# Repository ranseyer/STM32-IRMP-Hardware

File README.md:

View this project on [CADLAB.io](https://cadlab.io/project/2465). 

# STM32-IRMP-Hardware

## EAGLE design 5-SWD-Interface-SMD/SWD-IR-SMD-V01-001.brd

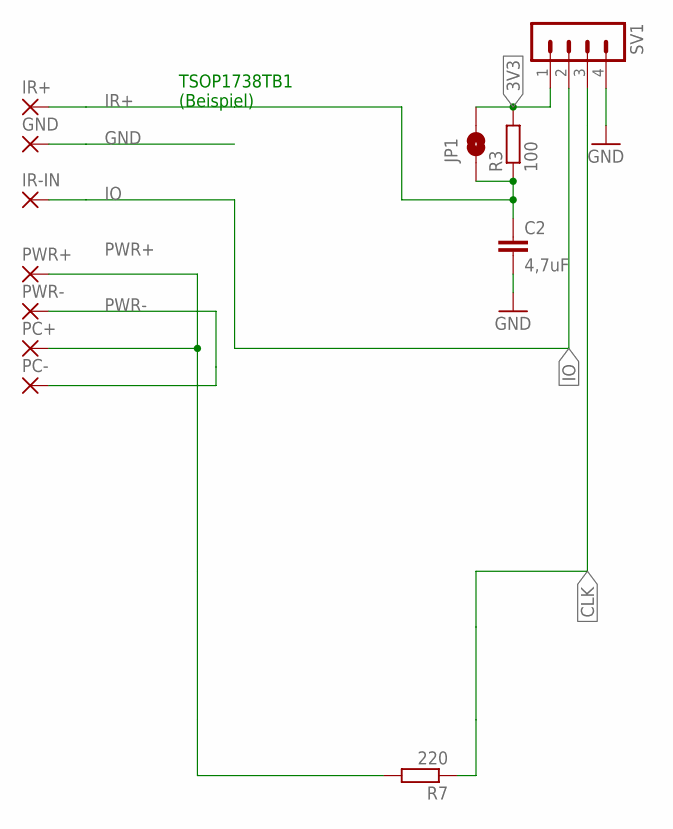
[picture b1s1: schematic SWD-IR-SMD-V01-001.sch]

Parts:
C2: 4,7uF; C1206K
GND: SMD2; SMD1,27-2,54
IR+: SMD2; SMD1,27-2,54
IR-IN: SMD2; SMD1,27-2,54
JP1: JUMPER-SMT_2_NO_NO-SILK; SMT-JUMPER_2_NO_NO-SILK
PC+: SMD2; SMD1,27-2,54
PC-: SMD2; SMD1,27-2,54
PWR+: SMD2; SMD1,27-2,54
PWR-: SMD2; SMD1,27-2,54
R3: 100; R0805W
R7: 220; R0805W
SV1: MA04-1

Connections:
3V3: JP1.2, R3.2, SV1.1
CLK: R7.1, SV1.3
GND: C2.2, GND.1, SV1.4
IO: IR-IN.1, SV1.2
IR+: C2.1, IR+.1, JP1.1, R3.1
PWR+: PC+.1, PWR+.1, R7.2
PWR-: PC-.1, PWR-.1

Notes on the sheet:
TSOP1738TB1 (Beispiel)

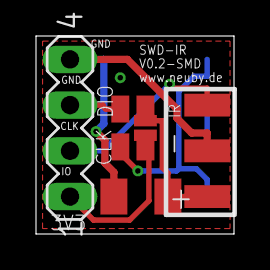
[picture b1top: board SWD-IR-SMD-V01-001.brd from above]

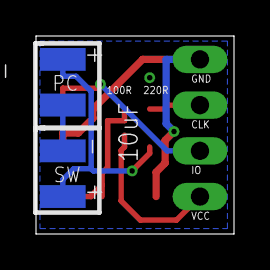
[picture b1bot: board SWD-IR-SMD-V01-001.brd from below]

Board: 2 copper layers, 11.0 x 11.0 mm, 12 parts (4 on the bottom side), 7 nets.

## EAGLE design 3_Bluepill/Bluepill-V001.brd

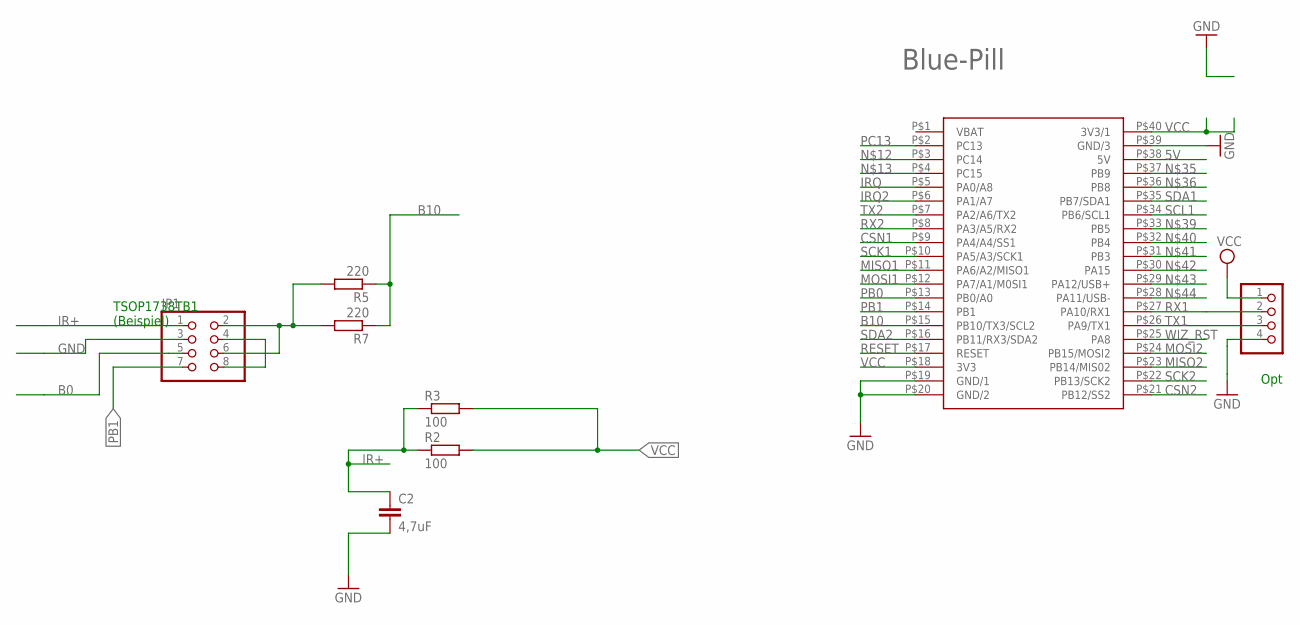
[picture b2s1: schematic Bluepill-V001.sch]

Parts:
C2: 4,7uF; C1206K
DBG: PINHD-1X04_2.54-S; 1X04-S
JP1: PINHD-2X4/90; 2X04/90
R2: 100; 0204/7
R3: 100; R0805W
R5: 220; 0204/7
R7: 220; R0805W
U$4: BLUEPILL

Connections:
5V: U$4.P$38 (5V)
B0: JP1.5
B10: R5.1, R7.1, U$4.P$15 (PB10/TX3/SCL2)
CSN1: U$4.P$9 (PA4/A4/SS1)
CSN2: U$4.P$21 (PB12/SS2)
GND: C2.2, DBG.4, JP1.3, U$4.P$19 (GND/1), U$4.P$20 (GND/2), U$4.P$39 (GND/3)
IR+: C2.1, JP1.1, R2.1, R3.1
IRQ: U$4.P$5 (PA0/A8)
IRQ2: U$4.P$6 (PA1/A7)
MISO1: U$4.P$11 (PA6/A2/MISO1)
MISO2: U$4.P$23 (PB14/MIS02)
MOSI1: U$4.P$12 (PA7/A1/M0SI1)
MOSI2: U$4.P$24 (PB15/MOSI2)
unnamed: JP1.4, JP1.8
unnamed: JP1.2, JP1.6, R5.2, R7.2
PB0: U$4.P$13 (PB0/A0)
PB1: JP1.7, U$4.P$14 (PB1)
PC13: U$4.P$2 (PC13)
RESET: U$4.P$17 (RESET)
RX1: DBG.2, U$4.P$27 (PA10/RX1)
RX2: U$4.P$8 (PA3/A5/RX2)
SCK1: U$4.P$10 (PA5/A3/SCK1)
SCK2: U$4.P$22 (PB13/SCK2)
SCL1: U$4.P$34 (PB6/SCL1)
SDA1: U$4.P$35 (PB7/SDA1)
SDA2: U$4.P$16 (PB11/RX3/SDA2)
TX1: DBG.3, U$4.P$26 (PA9/TX1)
TX2: U$4.P$7 (PA2/A6/TX2)
VCC: DBG.1, R2.2, R3.2, U$4.P$18 (3V3), U$4.P$40 (3V3/1)
WIZ_RST: U$4.P$25 (PA8)

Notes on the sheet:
TSOP1738TB1 (Beispiel)
Opt
Blue-Pill

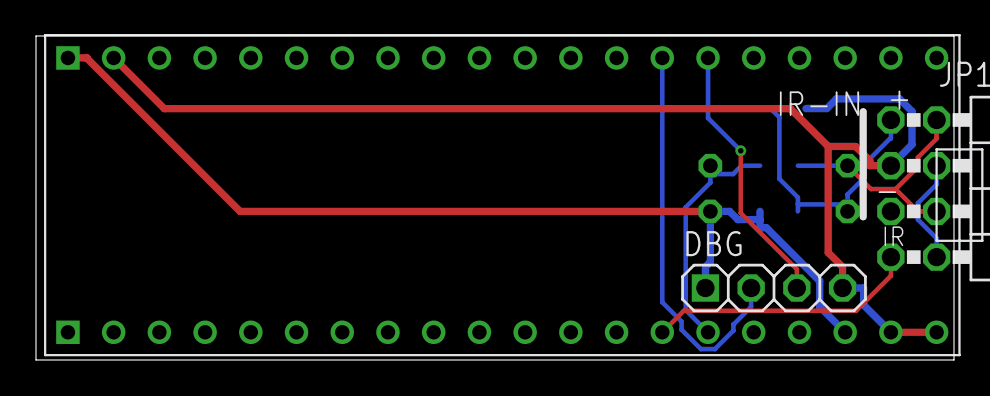
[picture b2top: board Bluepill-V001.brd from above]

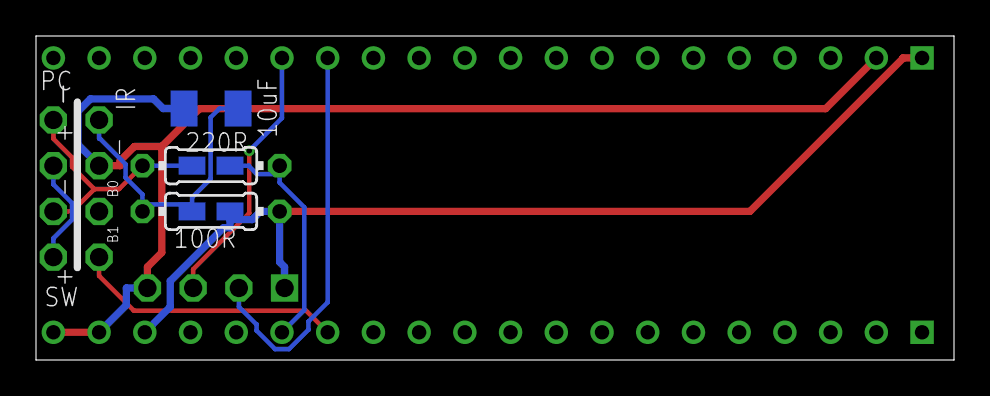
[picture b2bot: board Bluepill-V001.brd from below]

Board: 2 copper layers, 51.0 x 18.0 mm, 8 parts (5 on the bottom side), 9 nets.

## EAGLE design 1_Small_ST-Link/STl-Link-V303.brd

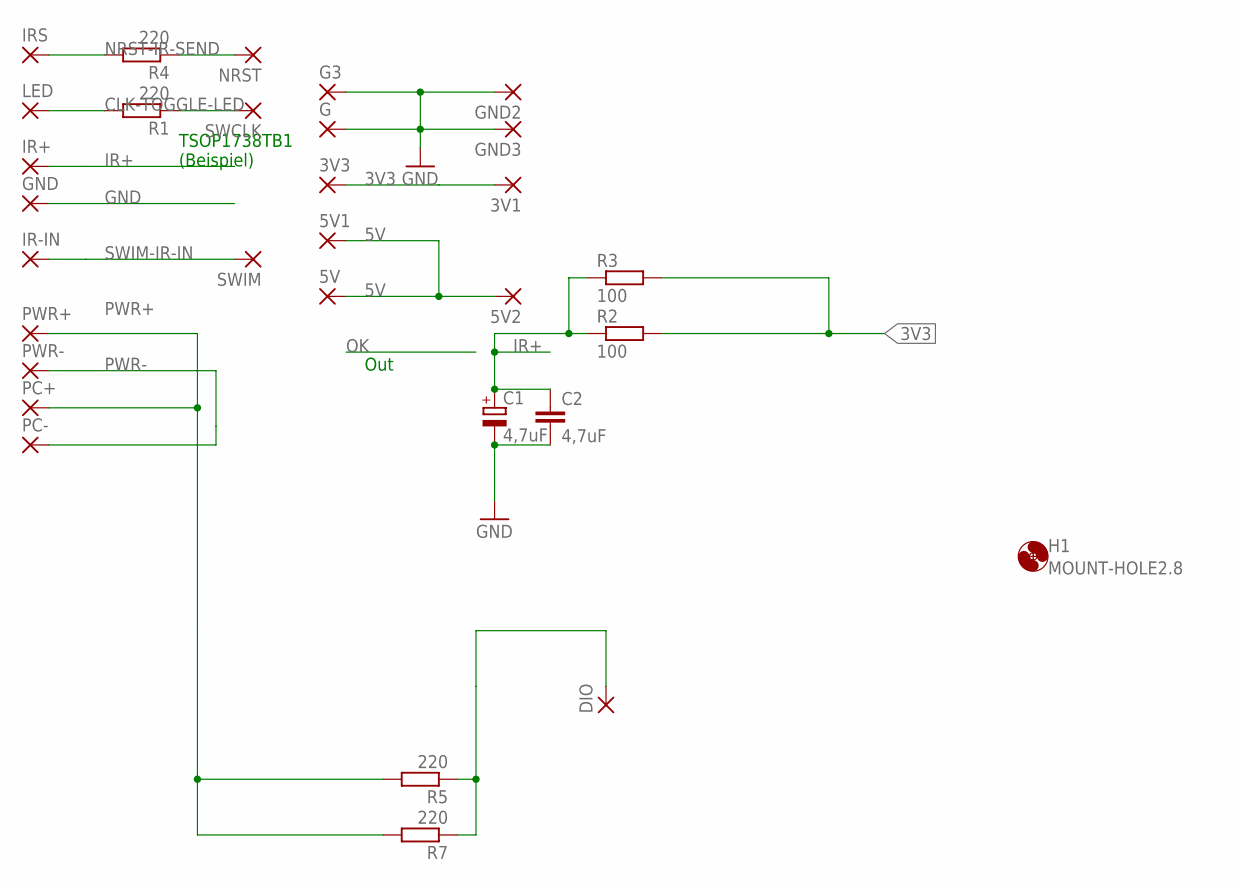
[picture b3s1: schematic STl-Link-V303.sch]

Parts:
3V1, 3V3, 5V, 5V1, 5V2: SMD2; SMD1,27-2,54
C1: 4,7uF; E1,8-4
C2: 4,7uF; C1206K
DIO: SMD2; SMD1,27-2,54
G, G3: SMD2; SMD1,27-2,54
GND, GND2, GND3: SMD2; SMD1,27-2,54
H1: MOUNT-HOLE2.8; 2,8
IR+: SMD2; SMD1,27-2,54
IR-IN: SMD2; SMD1,27-2,54
IRS: SMD2; SMD1,27-2,54
LED: SMD2; SMD1,27-2,54
NRST: SMD2; SMD1,27-2,54
PC+: SMD2; SMD1,27-2,54
PC-: SMD2; SMD1,27-2,54
PWR+: SMD2; SMD1,27-2,54
PWR-: SMD2; SMD1,27-2,54
R1, R4, R7: 220; R0805W
R2: 100; 0204/7
R3: 100; R0805W
R5: 220; 0204/7
SWCLK: SMD2; SMD1,27-2,54
SWIM: SMD2; SMD1,27-2,54

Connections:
3V3: 3V1.1, 3V3.1, R2.2, R3.2
5V: 5V.1, 5V1.1, 5V2.1
CLK-TOGGLE-LED: R1.1, SWCLK.1
DIO-EINSCH: DIO.1, R5.1, R7.1
GND: C1.-, C2.2, G.1, G3.1, GND.1, GND2.1, GND3.1
IR+: C1.+, C2.1, IR+.1, R2.1, R3.1
unnamed: NRST.1, R4.1
unnamed: LED.1, R1.2
NRST-IR-SEND: IRS.1, R4.2
PWR+: PC+.1, PWR+.1, R5.2, R7.2
PWR-: PC-.1, PWR-.1
SWIM-IR-IN: IR-IN.1, SWIM.1

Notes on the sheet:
Out
TSOP1738TB1 (Beispiel)

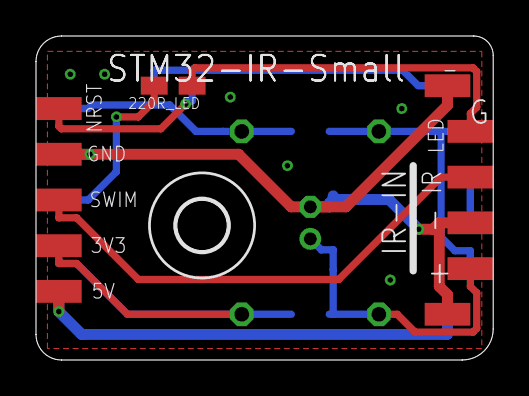
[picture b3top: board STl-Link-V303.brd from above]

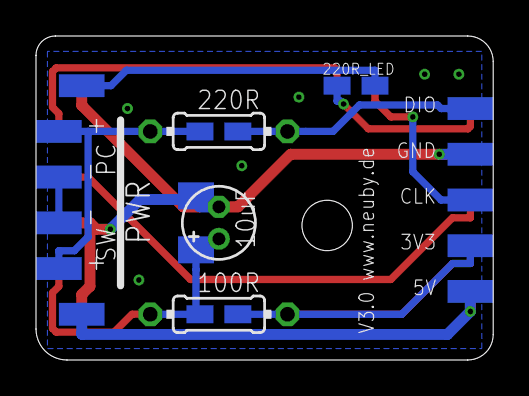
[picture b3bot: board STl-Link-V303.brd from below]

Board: 2 copper layers, 25.4 x 18.0 mm, 31 parts (18 on the bottom side), 12 nets.

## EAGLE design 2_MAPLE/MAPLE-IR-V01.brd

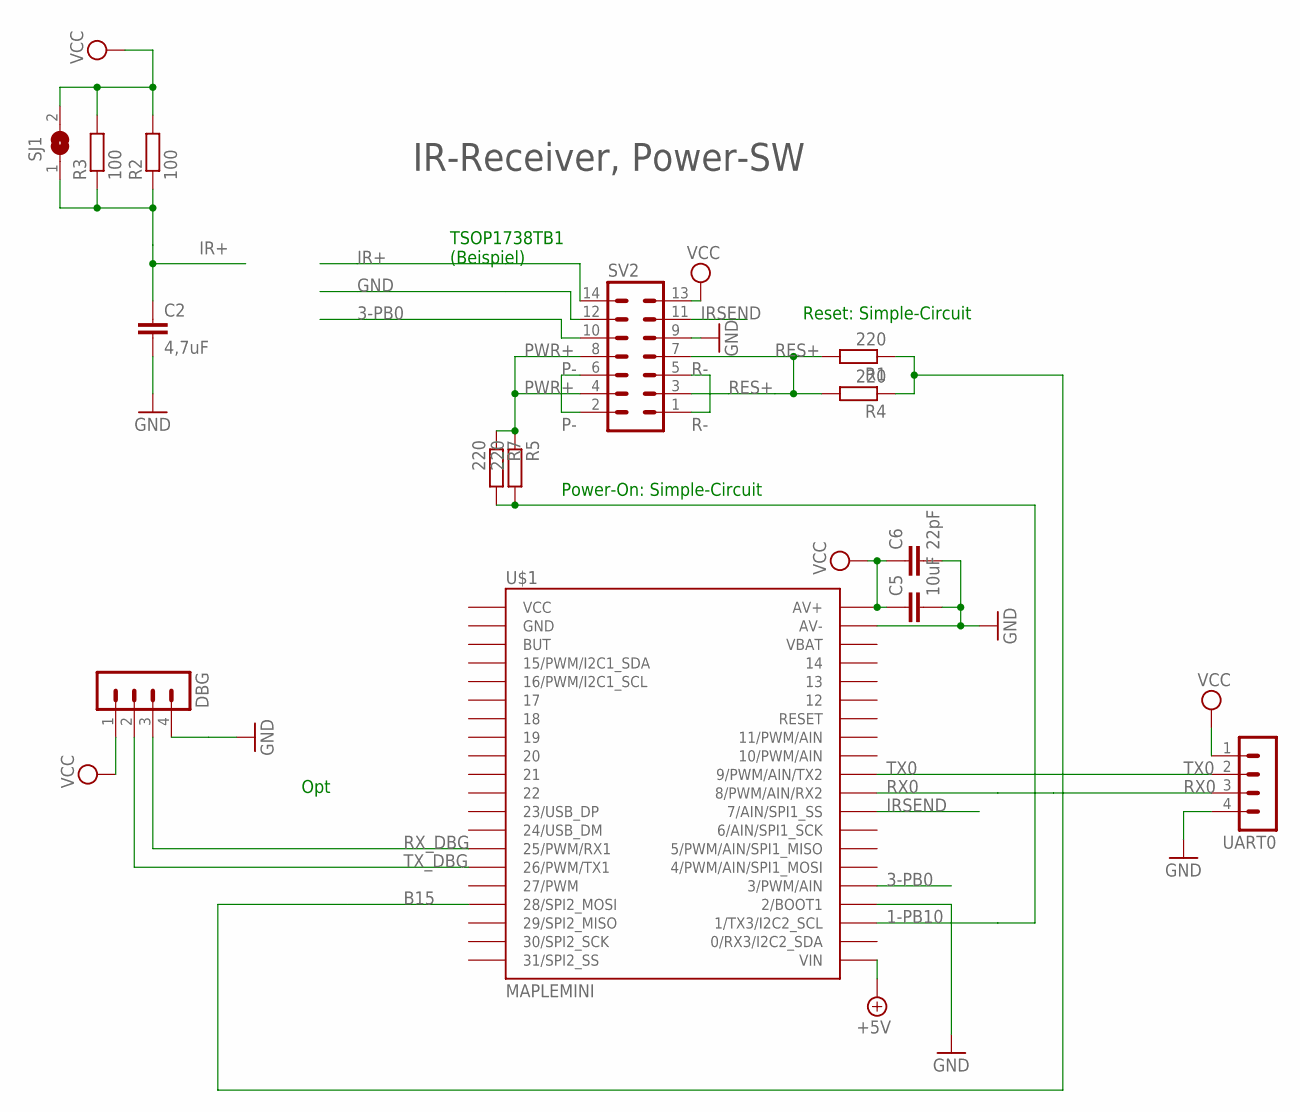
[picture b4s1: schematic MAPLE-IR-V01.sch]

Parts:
C2: 4,7uF; C1206K
C5: 10uF; C1210
C6: 22pF; C0805
DBG: MA04-1
R1, R5: 220; 0204/7
R2: 100; 0204/7
R3: 100; R0805W
R4, R7: 220; R0805W
SJ1: SJ
SV2: MA07-2
U$1: MAPLEMINI; 20-DIP
UART0: MA04-1

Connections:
1-PB10: R5.2, R7.2, U$1.23 (1/TX3/I2C2_SCL)
3-PB0: SV2.10, U$1.25 (3/PWM/AIN)
+5V: U$1.21 (VIN)
B15: R1.1, R4.1, U$1.17 (28/SPI2_MOSI)
GND: C2.2, C5.2, C6.2, DBG.4, SV2.9, SV2.12, U$1.24 (2/BOOT1), U$1.39 (AV-), UART0.4
IR+: C2.1, R2.1, R3.1, SJ1.1, SV2.14
IRSEND: SV2.11, U$1.29 (7/AIN/SPI1_SS)
P-: SV2.2, SV2.6
PWR+: R5.1, R7.1, SV2.4, SV2.8
R-: SV2.1, SV2.5
RES+: R1.2, R4.2, SV2.3, SV2.7
RX0: U$1.30 (8/PWM/AIN/RX2), UART0.3
RX_DBG: DBG.3, U$1.14 (25/PWM/RX1)
TX0: U$1.31 (9/PWM/AIN/TX2), UART0.2
TX_DBG: DBG.2, U$1.15 (26/PWM/TX1)
VCC: C5.1, C6.1, DBG.1, R2.2, R3.2, SJ1.2, SV2.13, U$1.40 (AV+), UART0.1

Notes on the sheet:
Opt
TSOP1738TB1 (Beispiel)
Power-On: Simple-Circuit
IR-Receiver, Power-SW
Reset: Simple-Circuit

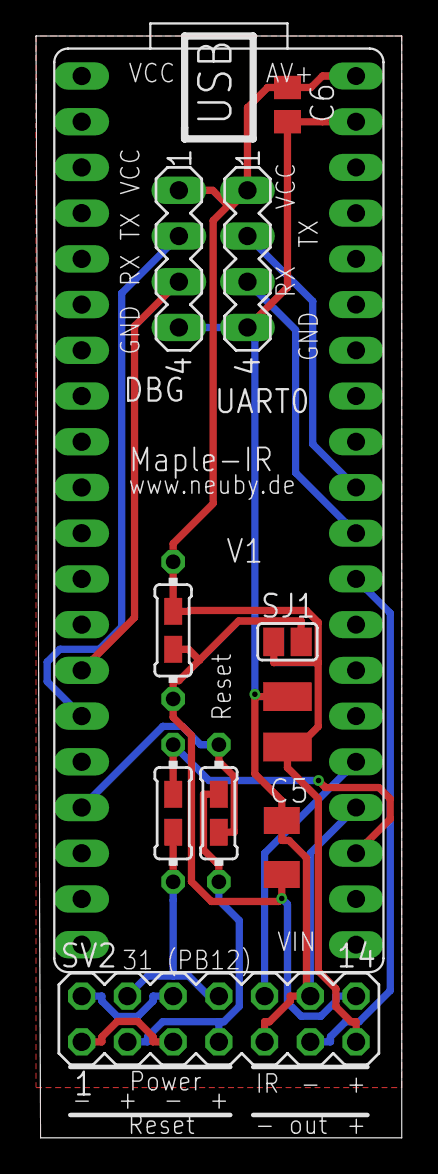
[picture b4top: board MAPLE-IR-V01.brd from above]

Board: 2 copper layers, 20.3 x 61.2 mm, 14 parts (0 on the bottom side), 15 nets.

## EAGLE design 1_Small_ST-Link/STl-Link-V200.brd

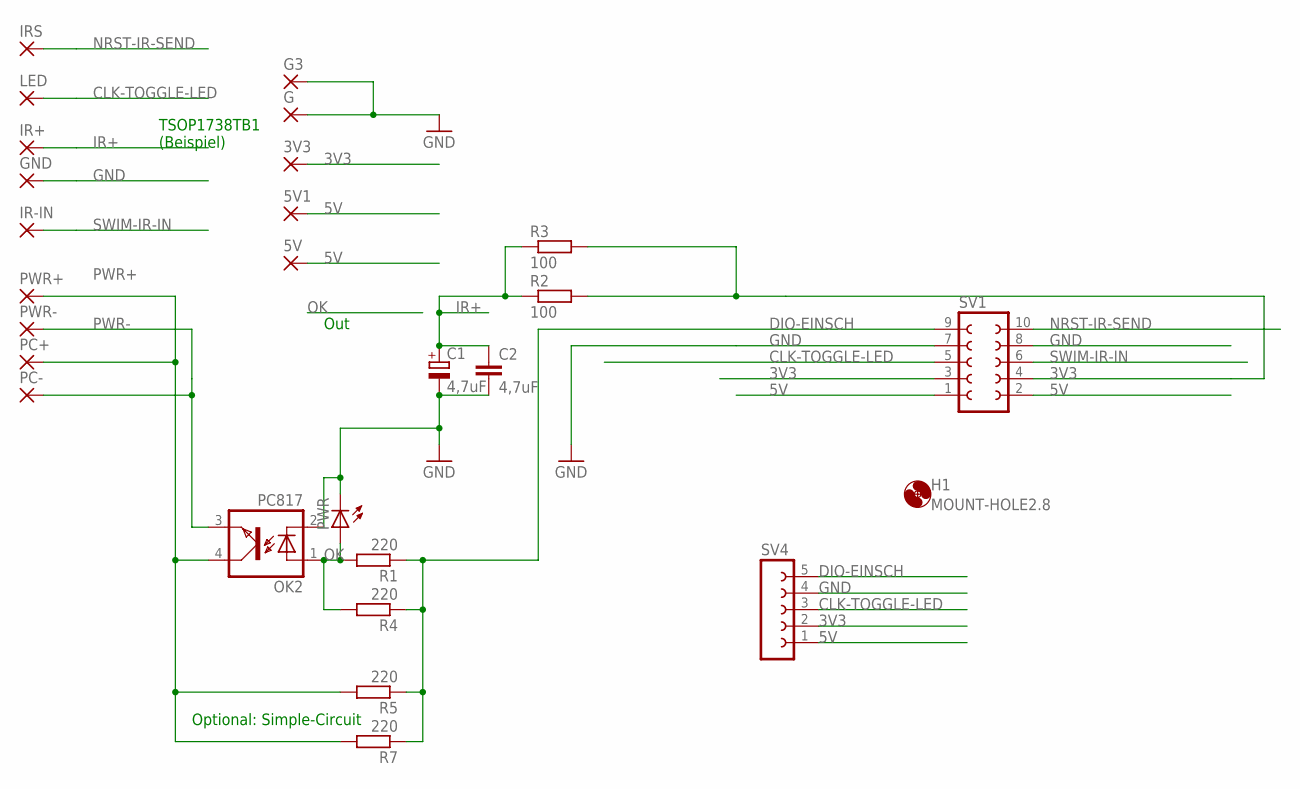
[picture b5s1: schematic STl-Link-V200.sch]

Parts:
3V3, 5V, 5V1: SMD2; SMD1,27-2,54
C1: 4,7uF; E1,8-4
C2: 4,7uF; C1206K
G, G3: SMD2; SMD1,27-2,54
GND: SMD2; SMD1,27-2,54
H1: MOUNT-HOLE2.8; 2,8
IR+: SMD2; SMD1,27-2,54
IR-IN: SMD2; SMD1,27-2,54
IRS: SMD2; SMD1,27-2,54
LED: SMD2; SMD1,27-2,54
OK2: PC817; DIL04
PC+: SMD2; SMD1,27-2,54
PC-: SMD2; SMD1,27-2,54
PWR: LEDCHIPLED_1206; CHIPLED_1206
PWR+: SMD2; SMD1,27-2,54
PWR-: SMD2; SMD1,27-2,54
R1, R5: 220; 0204/7
R2: 100; 0204/7
R3: 100; R0805W
R4, R7: 220; R0805W
SV1: FE05-2
SV4: FE05-1

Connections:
3V3: 3V3.1, R2.2, R3.2, SV1.3, SV1.4, SV4.2
5V: 5V.1, 5V1.1, SV1.1, SV1.2, SV4.1
CLK-TOGGLE-LED: LED.1, SV1.5, SV4.3
DIO-EINSCH: R1.1, R4.1, R5.1, R7.1, SV1.9, SV4.5
GND: C1.-, C2.2, G.1, G3.1, GND.1, OK2.2 (C), PWR.C, SV1.7, SV1.8, SV4.4
IR+: C1.+, C2.1, IR+.1, R2.1, R3.1
NRST-IR-SEND: IRS.1, SV1.10
OK: OK2.1 (A), PWR.A, R1.2, R4.2
PWR+: OK2.4 (COL), PC+.1, PWR+.1, R5.2, R7.2
PWR-: OK2.3 (EMIT), PC-.1, PWR-.1
SWIM-IR-IN: IR-IN.1, SV1.6

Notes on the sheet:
Out
TSOP1738TB1 (Beispiel)
Optional: Simple-Circuit

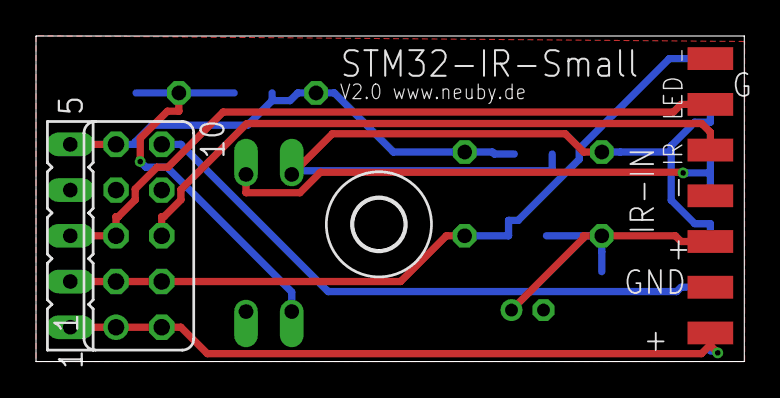
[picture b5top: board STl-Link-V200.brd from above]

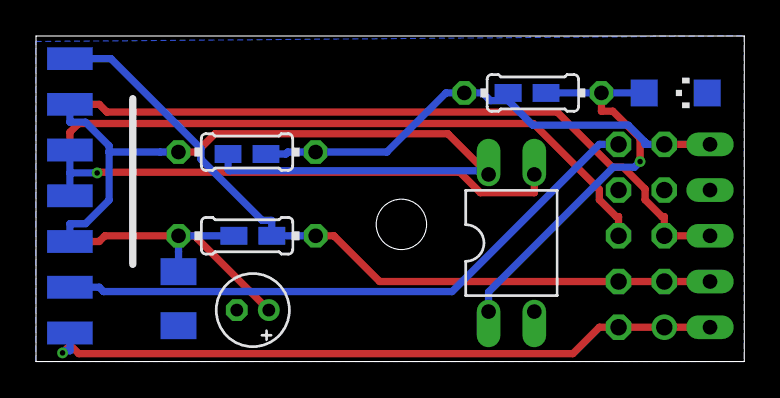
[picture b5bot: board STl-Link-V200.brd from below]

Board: 2 copper layers, 39.4 x 18.1 mm, 27 parts (17 on the bottom side), 11 nets.

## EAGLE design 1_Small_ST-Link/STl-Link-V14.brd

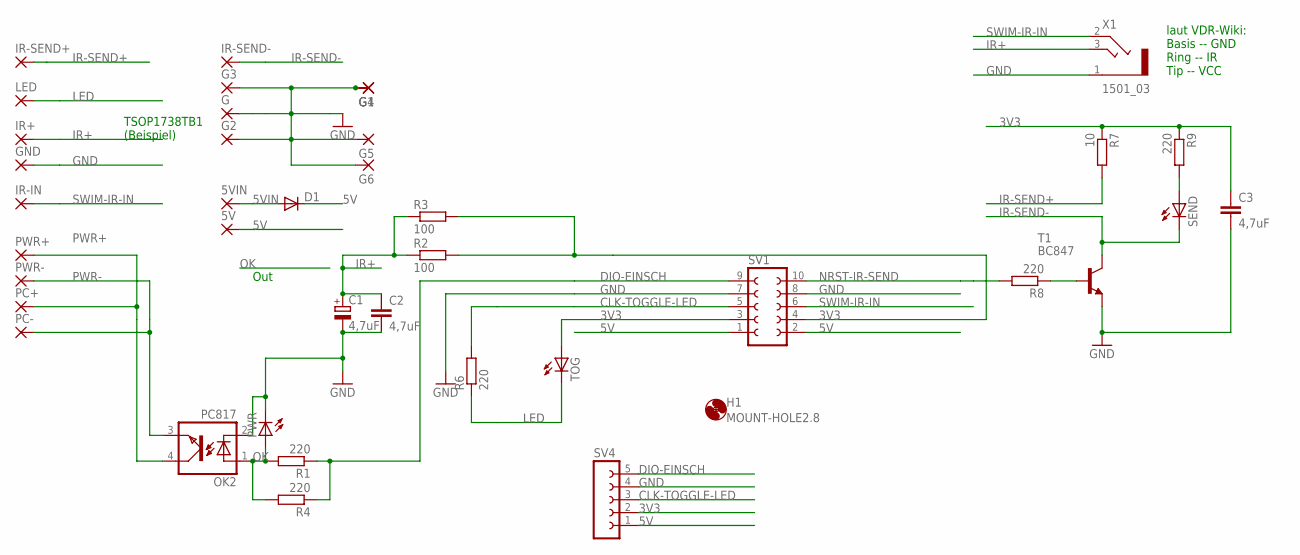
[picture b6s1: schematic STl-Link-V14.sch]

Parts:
5V, 5VIN: SMD2; SMD1,27-2,54
C1: 4,7uF; E1,8-4
C2, C3: 4,7uF; C1206K
D1: DIODE-SOD123; SOD123
G, G1, G2, G3, G4, G5, G6: SMD2; SMD1,27-2,54
GND: SMD2; SMD1,27-2,54
H1: MOUNT-HOLE2.8; 2,8
IR+: SMD2; SMD1,27-2,54
IR-IN: SMD2; SMD1,27-2,54
IR-SEND+: SMD2; SMD1,27-2,54
IR-SEND-: SMD2; SMD1,27-2,54
LED: SMD2; SMD1,27-2,54
OK2: PC817; DIL04
PC+: SMD2; SMD1,27-2,54
PC-: SMD2; SMD1,27-2,54
PWR: LEDCHIPLED_1206; CHIPLED_1206
PWR+: SMD2; SMD1,27-2,54
PWR-: SMD2; SMD1,27-2,54
R1: 220; 0204/7
R2: 100; 0204/7
R3: 100; R0805W
R4, R6, R8, R9: 220; R0805W
R7: 10; R0805W
SEND: LEDCHIPLED_1206; CHIPLED_1206
SV1: FE05-2
SV4: FE05-1
T1: BC847; SOT23
TOG: LEDCHIPLED_1206; CHIPLED_1206
X1: 1501_03

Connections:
3V3: C3.1, R2.2, R3.2, R7.1, R9.1, SV1.3, SV1.4, SV4.2, TOG.A
5V: 5V.1, D1.C, SV1.1, SV1.2, SV4.1
5VIN: 5VIN.1, D1.A
CLK-TOGGLE-LED: R6.2, SV1.5, SV4.3
DIO-EINSCH: R1.1, R4.1, SV1.9, SV4.5
GND: C1.-, C2.2, C3.2, G.1, G1.1, G2.1, G3.1, G4.1, G5.1, G6.1, GND.1, OK2.2 (C), PWR.C, SV1.7, SV1.8, SV4.4, T1.2 (E), X1.1
IR+: C1.+, C2.1, IR+.1, R2.1, R3.1, X1.3
IR-SEND+: IR-SEND+.1, R7.2
IR-SEND-: IR-SEND-.1, SEND.C, T1.3 (C)
LED: LED.1, R6.1, TOG.C
unnamed: R9.2, SEND.A
unnamed: R8.1, T1.1 (B)
NRST-IR-SEND: R8.2, SV1.10
OK: OK2.1 (A), PWR.A, R1.2, R4.2
PWR+: OK2.4 (COL), PC+.1, PWR+.1
PWR-: OK2.3 (EMIT), PC-.1, PWR-.1
SWIM-IR-IN: IR-IN.1, SV1.6, X1.2

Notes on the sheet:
Out
laut VDR-Wiki: Basis -- GND Ring -- IR Tip -- VCC
TSOP1738TB1 (Beispiel)

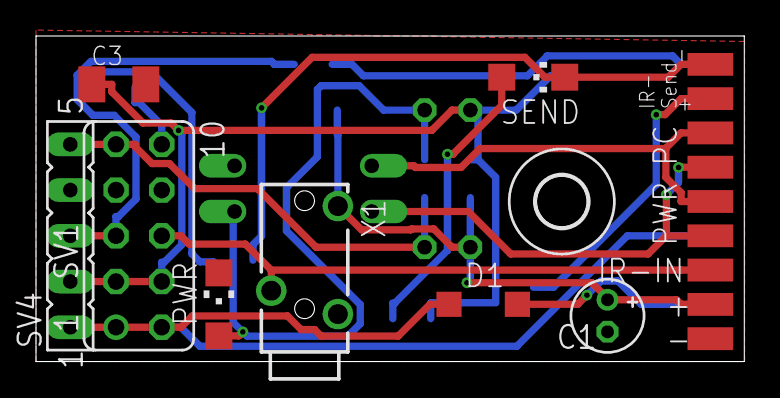
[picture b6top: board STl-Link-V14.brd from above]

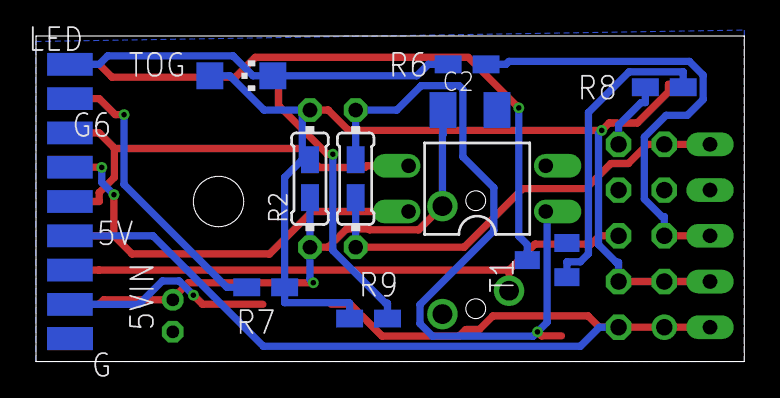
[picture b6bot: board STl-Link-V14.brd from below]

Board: 2 copper layers, 39.4 x 18.1 mm, 40 parts (22 on the bottom side), 17 nets.

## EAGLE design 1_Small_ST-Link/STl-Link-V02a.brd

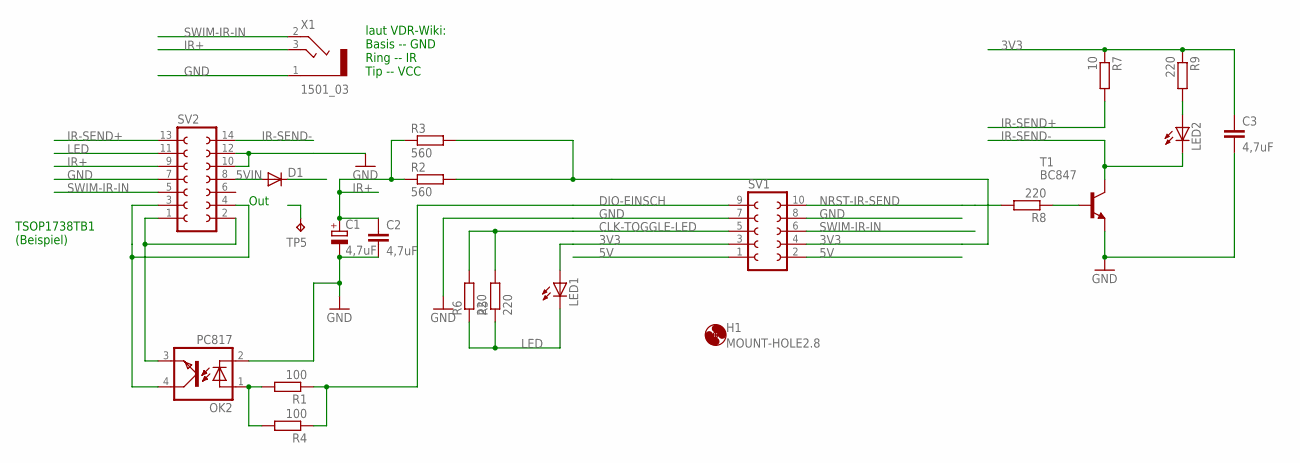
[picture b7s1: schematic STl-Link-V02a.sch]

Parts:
C1: 4,7uF; E1,8-4
C2, C3: 4,7uF; C1206K
D1: DIODE-SOD123; SOD123
H1: MOUNT-HOLE2.8; 2,8
LED1, LED2: LEDCHIPLED_1206; CHIPLED_1206
OK2: PC817; DIL04
R1: 100; 0204/7
R2: 560; 0204/7
R3: 560; R0805W
R4: 100; R0805W
R5: 220; 0204/7
R6, R8, R9: 220; R0805W
R7: 10; R0805W
SV1: FE05-2
SV2: FE07-2W
T1: BC847; SOT23
TP5: TPB1,27; B1,27
X1: 1501_03

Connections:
3V3: C3.1, LED1.A, R2.2, R3.2, R7.1, R9.1, SV1.3, SV1.4
5V: D1.C, SV1.1, SV1.2
5VIN: D1.A, SV2.8
CLK-TOGGLE-LED: R5.2, R6.2, SV1.5
DIO-EINSCH: R1.1, R4.1, SV1.9
GND: C1.-, C2.2, C3.2, OK2.2 (C), SV1.7, SV1.8, SV2.7, SV2.10, SV2.12, T1.2 (E), X1.1
IR+: C1.+, C2.1, R2.1, R3.1, SV2.9, X1.3
IR-SEND+: R7.2, SV2.13
IR-SEND-: LED2.C, SV2.14, T1.3 (C)
LED: LED1.C, R5.1, R6.1, SV2.11
unnamed: LED2.A, R9.2
unnamed: OK2.1 (A), R1.2, R4.2
unnamed: R8.1, T1.1 (B)
unnamed: OK2.3 (EMIT), SV2.1, SV2.2
NRST-IR-SEND: R8.2, SV1.10
OK2: OK2.4 (COL), SV2.3, SV2.4
SWIM-IR-IN: SV1.6, SV2.5, TP5.TP, X1.2

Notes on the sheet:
Out
laut VDR-Wiki: Basis -- GND Ring -- IR Tip -- VCC
TSOP1738TB1 (Beispiel)

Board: 2 copper layers, 22 parts (10 on the bottom side), 17 nets, no tracks yet.

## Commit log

2014-10-07 :lollipop: Added .gitattributes & .gitignore files
2014-10-07 1st draft
2014-10-07 Schematic export
2014-10-17 V2
    +TSOP Fix
    +OC moved
    -T for IR-Send
    -...
2014-10-19 V3 Lot of Changes
    eagle-files fallback
    other programmer
    separate pins
    optimized layout
2014-11-11 Final V1 Layout
2016-05-06 V2 PCB
2016-07-15 V2 Doku
2017-02-16 MAPLE Version
2017-04-14 Schematic +board export
2017-04-14 Docs
2017-04-14 cleanup
2018-02-13 V3 Small for STLinks
2018-02-13 Fix labeling
2018-02-24 LED removed
2020-01-18 SWD Version
    ((and Bluepill))
2020-01-18 V003
2020-01-21 beschriftung
2020-01-31 SMD Version
2020-02-08 Backlink to CADLAB.io has been added.

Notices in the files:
parts and their libraries:
SparkFun-Jumpers: Licensing: Creative Commons ShareAlike 4.0 International - https://creativecommons.org/licenses/by-sa/4.0
